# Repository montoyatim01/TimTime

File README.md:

# TimTime
Open Source Timecode Lock Box

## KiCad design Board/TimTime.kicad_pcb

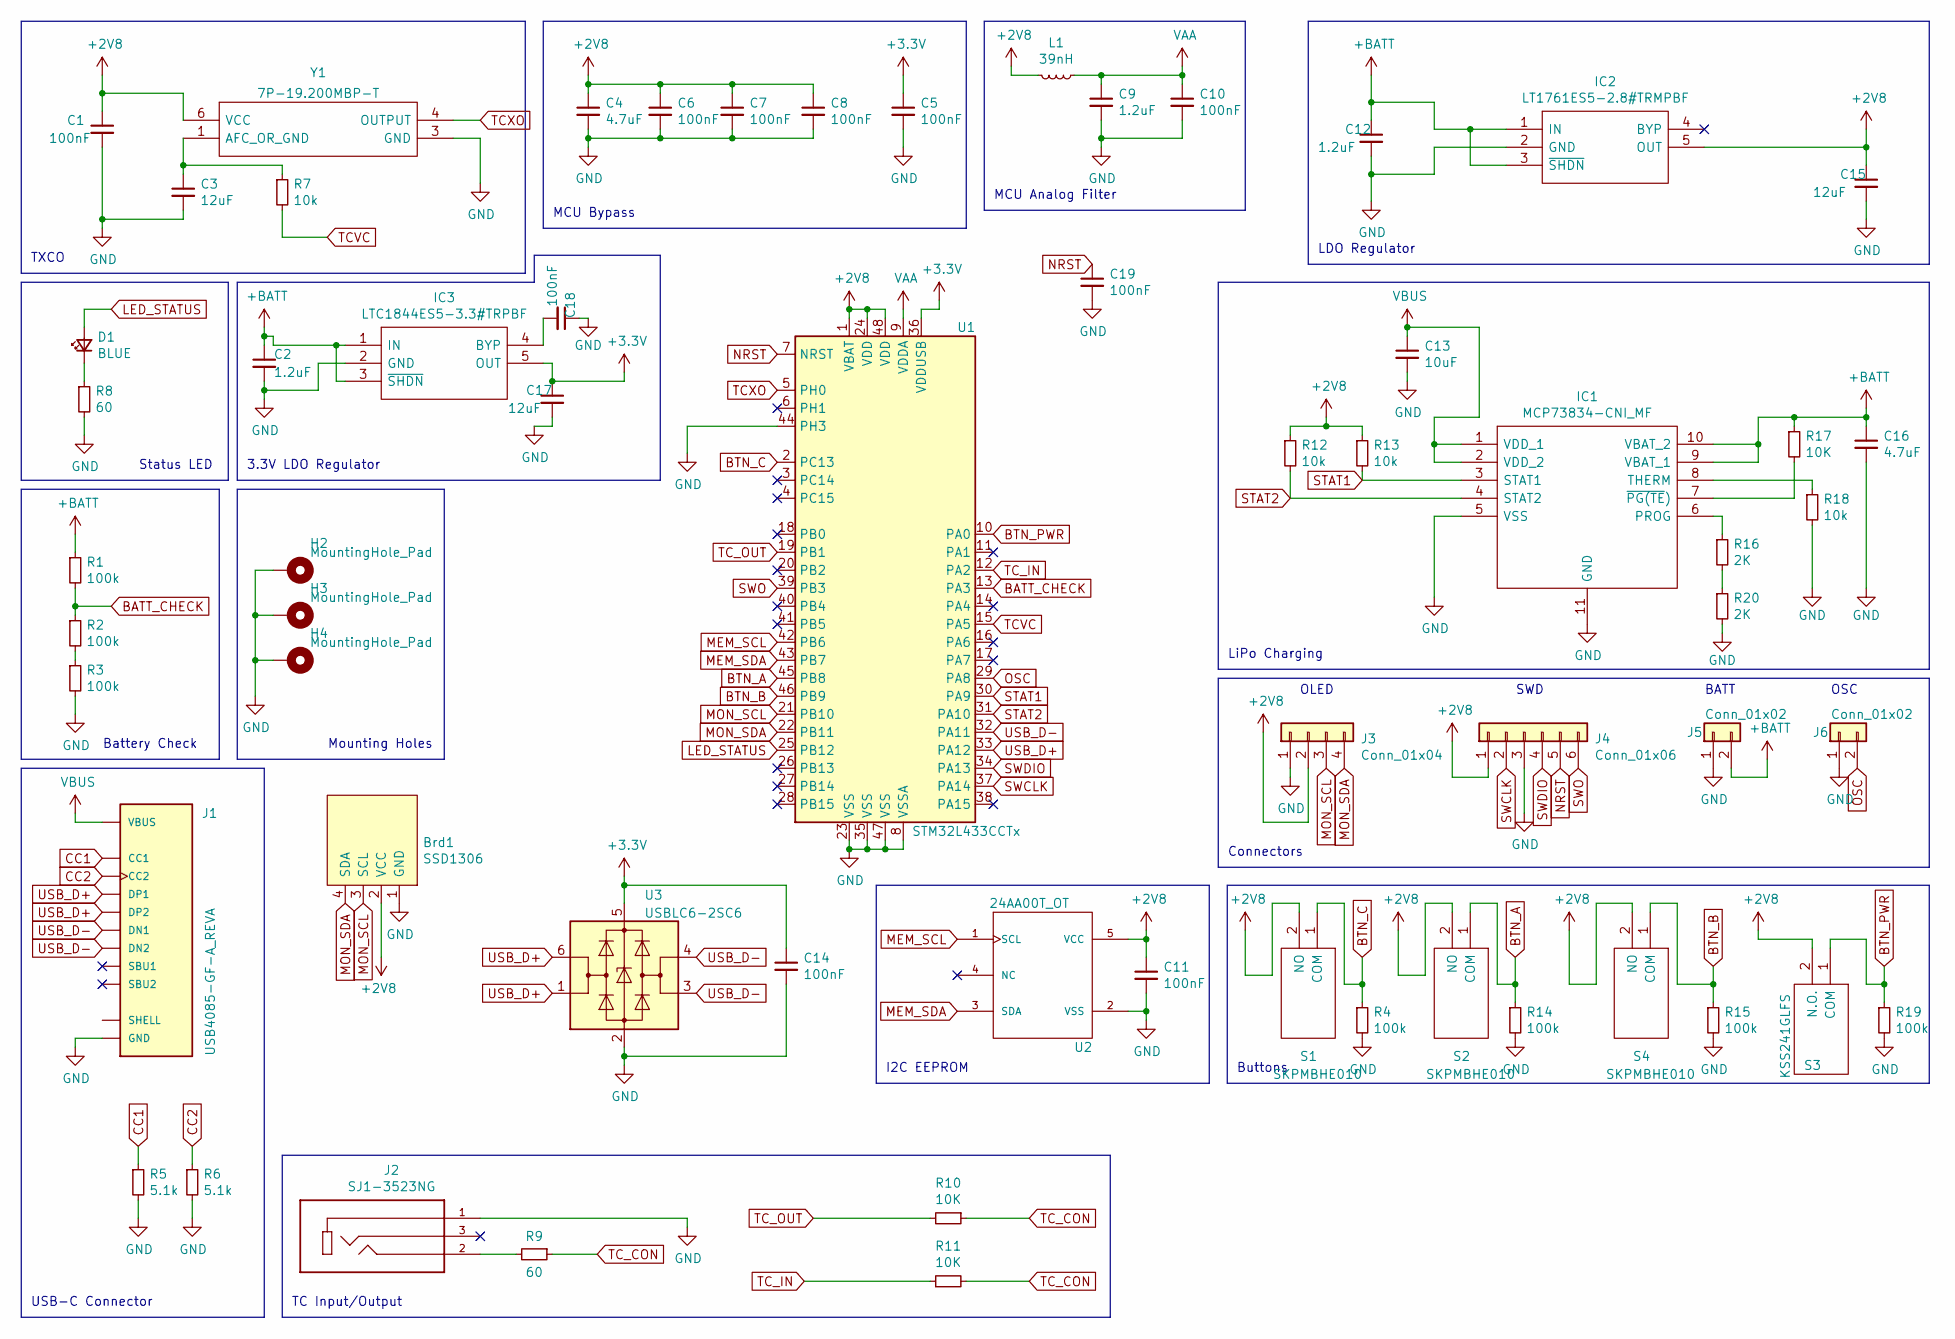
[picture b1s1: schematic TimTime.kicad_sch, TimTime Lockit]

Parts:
Brd1: SSD1306; 128x64OLED
C1, C5, C6, C7, C8, C10, C11, C14, C18, C19: 100nF; C_0603_1608Metric_Pad1.08x0.95mm_HandSolder
C2, C9, C12: 1.2uF; C_0603_1608Metric_Pad1.08x0.95mm_HandSolder
C3, C15, C17: 12uF; C_0603_1608Metric_Pad1.08x0.95mm_HandSolder
C4, C16: 4.7uF; C_0603_1608Metric_Pad1.08x0.95mm_HandSolder
C13: 10uF; C_0603_1608Metric_Pad1.08x0.95mm_HandSolder
D1: BLUE; LED_1206_3216Metric_Pad1.42x1.75mm_HandSolder
H2, H3, H4: MountingHole_Pad; MountingHole_3.2mm_M3_Pad_Via
IC1: MCP73834-CNI_MF; SON50P300X300X100-11N-D; Manufacturer_Part_Number MCP73834-CNI/MF; Mouser Part Number 579-MCP73834-CNI/MF
IC2: LT1761ES5-2.8#TRMPBF; SOT95P280X100-5N; Manufacturer_Part_Number LT1761ES5-2.8#TRMPBF; Mouser Part Number 584-1761ES5-2.8TMPF
IC3: LTC1844ES5-3.3#TRPBF; SOT95P280X100-5N; Manufacturer_Part_Number LT1761ES5-2.8#TRMPBF; Mouser Part Number 584-1761ES5-2.8TMPF
J1: USB4085-GF-A_REVA; GCT_USB4085-GF-A_REVA; PARTREV A2
J2: SJ1-3523NG; CUI_SJ1-3523NG; PARTREV 1.01
J3: Conn_01x04; PinHeader_1x04_P2.54mm_Vertical
J4: Conn_01x06; PinHeader_1x06_P2.54mm_Vertical
J5, J6: Conn_01x02; PinHeader_1x02_P2.54mm_Vertical
L1: 39nH; L_0603_1608Metric_Pad1.05x0.95mm_HandSolder
R1, R2, R3, R4, R14, R15, R19: 100k; R_0603_1608Metric_Pad0.98x0.95mm_HandSolder
R5, R6: 5.1k; R_0603_1608Metric_Pad0.98x0.95mm_HandSolder
R7, R12, R13, R18: 10k; R_0603_1608Metric_Pad0.98x0.95mm_HandSolder
R8, R9: 60; R_0603_1608Metric_Pad0.98x0.95mm_HandSolder
R10, R11, R17: 10K; R_0603_1608Metric_Pad0.98x0.95mm_HandSolder
R16, R20: 2K; R_0603_1608Metric_Pad0.98x0.95mm_HandSolder
S1, S2, S4: SKPMBHE010; Manufacturer_Part_Number SKPMBHE010; Mouser Part Number 688-SKPMBHE010
S3: KSS241GLFS; Manufacturer_Part_Number KSS241GLFS; Mouser Part Number 611-KSS241GLFS
U1: STM32L433CCTx; LQFP-48_7x7mm_P0.5mm
U2: 24AA00T_OT; SOT95P280X145-5N
U3: USBLC6-2SC6; SOT-23-6
Y1: 7P-19.200MBP-T; 7P25000MBPT; Manufacturer_Part_Number 7P-25.000MBP-T; Mouser Part Number 717-7P-25.000MBP-T

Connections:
+2V8: Brd1.2 (VCC), C1.1, C4.1, C6.1, C7.1, C8.1, C11.1, C15.1, IC2.5 (OUT), J3.2, J4.1, L1.2, R12.1, R13.1, S1.2 (NO), S2.2 (NO), S3.2 (N.O.), S4.2 (NO), U1.1 (VBAT), U1.24 (VDD), U1.48 (VDD), U2.5 (VCC), Y1.6 (VCC)
+3V3: C5.1, C14.1, C17.1, IC3.5 (OUT), U1.36 (VDDUSB), U3.5 (VBUS)
+BATT: C2.1, C12.1, C16.1, IC1.9 (VBAT_1), IC1.10 (VBAT_2), IC2.1 (IN), IC2.3 (~SHDN), IC3.1 (IN), IC3.3 (~SHDN), J5.2, R1.1, R17.1
BATT_CHECK: R1.2, R2.1, U1.13 (PA3)
BTN_A: R14.1, S2.1 (COM), U1.45 (PB8)
BTN_B: R15.1, S4.1 (COM), U1.46 (PB9)
BTN_C: R4.1, S1.1 (COM), U1.2 (PC13)
BTN_PWR: R19.1, S3.1 (COM), U1.10 (PA0)
CC1: J1.A5 (CC1), R5.1
CC2: J1.B5 (CC2), R6.1
GND: Brd1.1 (GND), C1.2, C2.2, C3.2, C4.2, C5.2, C6.2, C7.2, C8.2, C9.2, C10.2, C11.2, C12.2, C13.2, C14.2, C15.2, C16.2, C17.2, C18.1, C19.2, H2.1, H3.1, H4.1, IC1.5 (VSS), IC1.11 (GND), IC2.2 (GND), IC3.2 (GND), J1.A1 (GND), J1.A12 (GND), J1.B1 (GND), J1.B12 (GND), J2.1, J3.1, J4.3, J5.1, J6.1, R3.2, R4.2, R5.2, R6.2, R8.2, R14.2, R15.2, R18.2, R19.2, R20.2, U1.8 (VSSA), U1.23 (VSS), U1.35 (VSS), U1.44 (PH3), U1.47 (VSS), U2.2 (VSS), U3.2 (GND), Y1.3 (GND)
LED_STATUS: D1.2 (A), U1.25 (PB12)
MEM_SCL: U1.42 (PB6), U2.1 (SCL)
MEM_SDA: U1.43 (PB7), U2.3 (SDA)
MON_SCL: Brd1.3 (SCL), J3.3, U1.21 (PB10)
MON_SDA: Brd1.4 (SDA), J3.4, U1.22 (PB11)
NRST: C19.1, J4.5, U1.7 (NRST)
unnamed: C3.1, R7.1, Y1.1 (AFC_OR_GND)
unnamed: C18.2, IC3.4 (BYP)
unnamed: D1.1 (K), R8.1
unnamed: IC1.6 (PROG), R16.1
unnamed: IC1.7 (~PG(TE)), R17.2
unnamed: IC1.8 (THERM), R18.1
unnamed: J1.P1 (SHELL), J1.P2 (SHELL), J1.P3 (SHELL), J1.P4 (SHELL)
unnamed: J2.2, R9.2
unnamed: R2.2, R3.1
unnamed: R16.2, R20.1
OSC: J6.2, U1.29 (PA8)
STAT1: IC1.3 (STAT1), R13.2, U1.30 (PA9)
STAT2: IC1.4 (STAT2), R12.2, U1.31 (PA10)
SWCLK: J4.2, U1.37 (PA14)
SWDIO: J4.4, U1.34 (PA13)
SWO: J4.6, U1.39 (PB3)
TCVC: R7.2, U1.15 (PA5)
TCXO: U1.5 (PH0), Y1.4 (OUTPUT)
TC_CON: R9.1, R10.1, R11.2
TC_IN: R11.1, U1.12 (PA2)
TC_OUT: R10.2, U1.19 (PB1)
USB_D+: J1.A6 (DP1), J1.B6 (DP2), U1.33 (PA12), U3.1 (I/O1), U3.6 (I/O1)
USB_D-: J1.A7 (DN1), J1.B7 (DN2), U1.32 (PA11), U3.3 (I/O2), U3.4 (I/O2)
VAA: C9.1, C10.1, L1.1, U1.9 (VDDA)
VBUS: C13.1, IC1.1 (VDD_1), IC1.2 (VDD_2), J1.A4 (VBUS), J1.A9 (VBUS), J1.B4 (VBUS), J1.B9 (VBUS)

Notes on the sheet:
TC Input/Output
Connectors
TXCO
Mounting Holes
LiPo Charging
Battery Check
USB-C Connector
3.3V LDO Regulator
MCU Bypass
SWD
LDO Regulator
Status LED
MCU Analog Filter
OLED
OSC
Buttons
I2C EEPROM
BATT

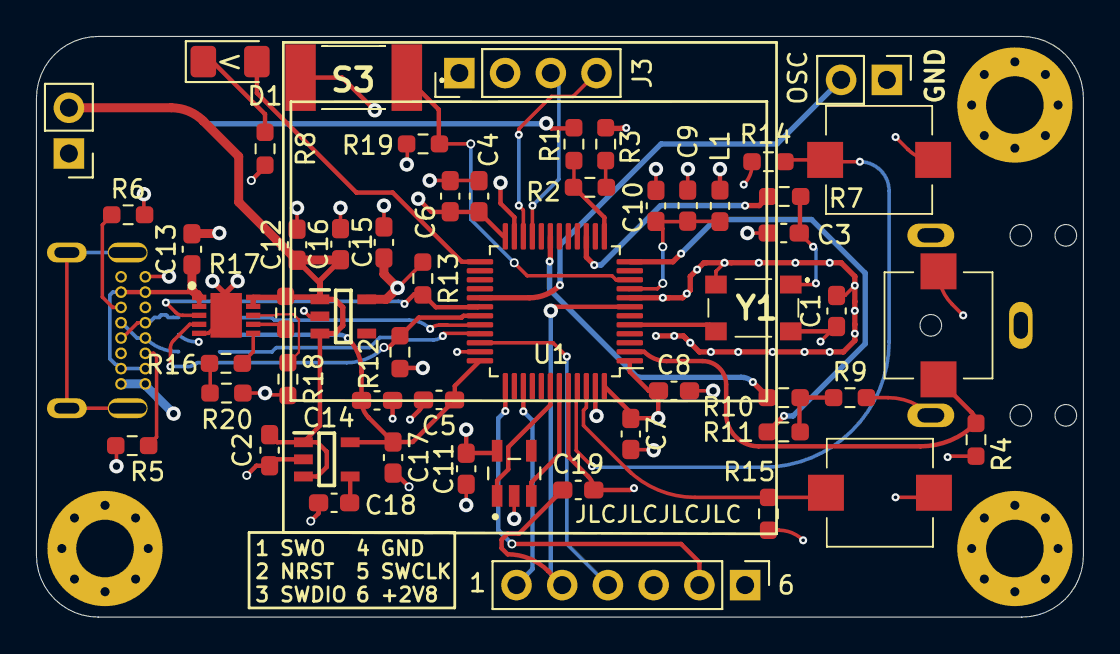
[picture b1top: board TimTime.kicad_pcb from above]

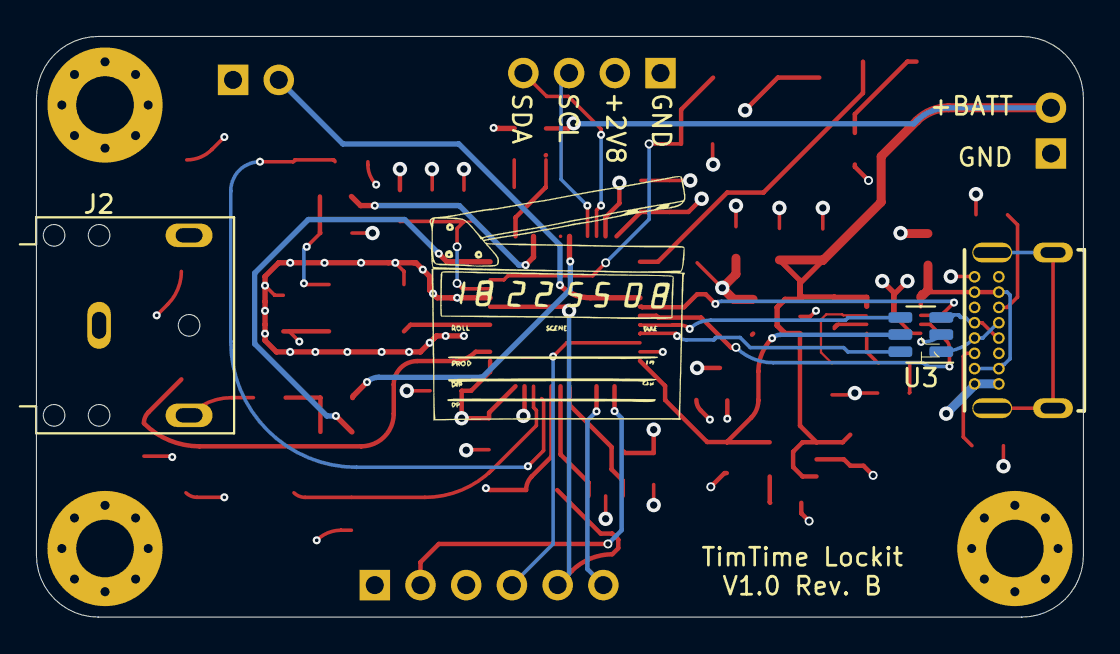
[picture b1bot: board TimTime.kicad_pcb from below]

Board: 4 copper layers, 58.2 x 32.3 mm, 61 parts (3 on the bottom side), 42 nets.

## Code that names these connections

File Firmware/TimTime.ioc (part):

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Mcu.Name=STM32L433C(B-C)Tx
Mcu.Package=LQFP48
Mcu.UserName=STM32L433CCTx
PA0.Mode=SYS_WakeUp0
PA0.Signal=SYS_WKUP1
PA10.GPIOParameters=GPIO_Label
PA10.GPIO_Label=STAT2
PA10.Signal=GPIO_Input
PA11.Mode=Device
PA11.Signal=USB_DM
PA12.Mode=Device
PA12.Signal=USB_DP
PA13\ (JTMS-SWDIO).Mode=Serial_Wire
PA13\ (JTMS-SWDIO).Signal=SYS_JTMS-SWDIO
PA14\ (JTCK-SWCLK).Mode=Serial_Wire
PA14\ (JTCK-SWCLK).Signal=SYS_JTCK-SWCLK
PA2.GPIOParameters=GPIO_Label
PA2.GPIO_Label=TC_IN
PA2.Signal=S_TIM2_CH3
PA3.GPIOParameters=GPIO_Label
PA3.GPIO_Label=BATT_CHECK
PA3.Signal=ADCx_IN8
PA5.GPIOParameters=GPIO_Label
PA5.GPIO_Label=TCVC
PA5.Signal=COMP_DAC12_group
PA8.GPIOParameters=GPIO_Label
PA8.GPIO_Label=OSC
PA8.Mode=Clock-out
PA8.Signal=RCC_MCO
PA9.GPIOParameters=GPIO_Label
PA9.GPIO_Label=STAT1
PA9.Signal=GPIO_Input
PB1.GPIOParameters=GPIO_Label
PB1.GPIO_Label=TC_OUT
PB1.Signal=GPIO_Output
PB10.GPIOParameters=GPIO_Label,GPIO_Pu
PB10.GPIO_Label=MON_SCL
PB10.GPIO_Pu=GPIO_PULLUP
PB10.Mode=I2C
PB10.Signal=I2C2_SCL
PB11.GPIOParameters=GPIO_Label,GPIO_Pu
PB11.GPIO_Label=MON_SDA
PB11.GPIO_Pu=GPIO_PULLUP
PB11.Mode=I2C
PB11.Signal=I2C2_SDA
PB12.GPIOParameters=GPIO_Label
PB12.GPIO_Label=LED_STATUS
PB12.Signal=GPIO_Output
PB6.GPIOParameters=GPIO_Label,GPIO_Pu
PB6.GPIO_Label=MEM_SCL
PB6.GPIO_Pu=GPIO_PULLUP
PB6.Mode=I2C
PB6.Signal=I2C1_SCL
PB7.GPIOParameters=GPIO_Label,GPIO_Pu
PB7.GPIO_Label=MEM_SDA
PB7.GPIO_Pu=GPIO_PULLUP
PB7.Mode=I2C
PB7.Signal=I2C1_SDA
PB8.GPIOParameters=GPIO_Label
PB8.GPIO_Label=BTN_A
PB8.Signal=GPIO_Input
PB9.GPIOParameters=GPIO_Label
PB9.GPIO_Label=BTN_B
PB9.Signal=GPIO_Input
PC13.Signal=GPIO_Input
PH0-OSC_IN\ (PH0).Mode=HSE-External-Clock-Source
PH0-OSC_IN\ (PH0).Signal=RCC_OSC_IN
RCC.HSE_VALUE=19200000
RCC.SYSCLKFreq_VALUE=24000000
RCC.SYSCLKSource=RCC_SYSCLKSOURCE_PLLCLK
board=custom

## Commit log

2021-05-01 V01 Schematic
    Initial schematic design
2021-05-04 Initial Board Layout
    Rough pass of component layout. Working down the overall footprint of the device. Also updated a couple components in the schematic.
2021-06-27 Layout/Routing
    Full V01 layout and routing
2021-07-08 Update layout
    Smaller footprint
2021-08-12 Updated routing
2021-08-14 V02 routing. VddUSB
2021-08-16 Finalize V02 routing
2021-08-18 Add additional button, include libraries
2021-10-17 V01 Gerbers
2021-11-13 Firmware Stems
2021-12-06 Refactoring
2021-12-13 Linker issues
2021-12-13 Build
2021-12-13 Linker
2021-12-13 Refactoring
    Almost complete with reformatting/implementation of most base features
2021-12-20 Menu V01
2022-01-24 Screen timeout, lock, initial power on/off
2022-01-25 Battery implementation, new method for button holds
2022-01-26 EEPROM Implementation, Calibration setting menu
2022-01-31 Finish calibration menus/checks, start user bit menu implementation
2022-02-04 TC Outputs Userbits, modify EEPROM
2022-02-27 V01B Board
2023-07-14 Backup
2023-07-14 Migration to PlatformIO
